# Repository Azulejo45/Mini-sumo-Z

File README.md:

### ┍━━━━━━━━━━━━»•»  «•«━━━━┑
#   ┕Zangetsu-MiniSumo┙        

### - Proyecto de mini sumo con la capacidad de ser controlado de manera bluetooth y automata. Equipado con 4 sensores:  2 laterales, 1 frontal y uno en la parte inferior, el de piso.
♥

## ..••°°━✦❘༻⋞ 〈 Autores  〉 ⋟༺❘✦━━°°••..

- ⋆ˊˎ-   ┌──༺♥༻❀**Velazquez Joaquim**❀༺♥༻
  
- ⋆ˊˎ-  **Rodriguez Thiago**

### *---16/3/2026---*

♥
## •*¨*•.¸¸☆*･ﾟ Especificaciones generales ﾟ･*☆¸¸.•*¨*•

˚₊· ͟͟͞͞➳❥ Dimensiones del robot: 10 cm x 10 cm x 4,5 cm.

˚₊· ͟͟͞͞➳❥ Consumo total: 7,4V.

˚₊· ͟͟͞͞➳❥ Corriente total: 800mA.

˚₊· ͟͟͞͞➳❥ Material de la carrocería: PLA.

˚₊· ͟͟͞͞➳❥ Peso (aproximado): 300g.
## ✭∞∞∞∞∞∞∞∞✭∞∞•,¸,.·' ✩ '·.,¸,•∞∞✭∞∞∞∞∞∞∞∞✭

♥
## Objetivo del proyecto
### ✩°｡𓂃𓏧︶︶︶︶︶︶︶︶┈୨•♡•୧┈︶︶︶︶︶︶︶𓂃𓏧｡°✩
_El objetivo principal de este proyecto es poner a prueba lo aprendido en años anteriores y este, pudiendo aplicarlo en el proceso de preparacion y  creacion de un robot modelo Mini-Sumo, siguiendo el reglamento de la liga nacional de robotica LNR, para que se encuentre en condiciones en poder participar en una competencia de esta misma_
### ✩°｡𓂃𓏧⌒⌒⌒⌒⌒⌒⌒⌒┈୨•♡•୧┈⌒⌒⌒⌒⌒⌒⌒⌒𓂃𓏧｡°✩
\
\
.
### ∘₊✧───∘₊✧───•-•⟮ ◆ ⟯•-•───✧₊∘───✧₊∘
## ˗ˏˋ ꒰ **Este proyecto fue realizado con algunos componentes en donde se puede llegan a encontrar:** ꒱ ˎˊ˗

- Micro: Esp32 C3 super mini.
 > Memoria: 400 KB SRAM, 4 MB Flash.Conectividad: Wi-Fi (2,4 GHz).\
 > Bluetooth 5.0 LE (Low Energy).\
 > Alimentación: Funciona a 3,3 V con entrada USB-C de 5 V.

- Bateria de Lipo.
 > Almacenamiento: 7,4V.\
 > 2 celdas (3,7V por celda)
  
- Sensor de piso: TCRT5000.
 > Voltaje de operación: 3.3V-5V.\
 > Dimensiones: 31 mm × 13 mm × 2 mm.\
 > Rango de detección: 30° más amplio.

- Sensor detector de obstáculos: HC-sr04.
 > Voltaje de operacion: 5V.\
 > Cantidad de pines: 4.\
 > Distancia de deteccion: 2 a 450cm.
 
- Motores: Micro motores Pololu 250RPM.
 > Dimensiones: 26x10x12mm.\
 > Voltaje de operacion: 6V.\
 > Torque maximo: 333Nm (Newton - metro).

- Puente H: DRV8833.
 > Dimensiones: 4 mm × 18,1 mm × 21,1 mm.\
 > Voltaje de operacion: 2.7V-10.8V.\
 > Corriente máxima de salida: 1,5A.
 ### ∘₊✧───∘₊✧──────✧₊∘───✧₊∘
\
.
## ╔══✬✩══╡˚✧Componentes utilizados✧˚╞══✩✬══╗
- ➸ *Esp32 C3 super mini.*
- ➸ *Bateria de Lipo.*
- ➸ *TCRT5000.*
- ➸ *HC-sr04.*
- ➸ *Micro motores Pololu 250RPM.*
- ➸ *DRV8833.*
## ╚═══*+:｡ . ｡:+*═══✮❁•°❀°•❁✮═══*+:｡ . ｡:+*═══╝
\
\
\
\
\
♥
# Diseño del circuito

## Descripcion del funcionamiento

El minisumo utiliza tres sensores para guiarse, con dos ubicados en los costados; otro en la parte frontal. Cuando un objeto entra en el rango del sensor frontal, el minisumo avanza hasta chocar contra dicho objeto. Esto siempre se cumple hasta que se quite la orden.\
Cuando uno de los sensores en los costados detectan algo cerca, se posiciona para estar de frente al objeto, retrocediendo y girando en direccion paralela a este.
Este mismo, utiliza el sensor de piso para evitar salirse del dohyo, detectyando la franja limite y volviendo para no estar tan vulnerable a cualquier empuje que lo saque de juego.

## Esquematico

## Layout de PCB

# Pasos a seguir para armar el mini-sumo
## ˚*•̩̩͙✩•̩̩͙*˚＊˚*•̩̩͙✩•̩̩͙*˚＊˚*•̩̩͙✩•̩̩͙*˚＊˚*•̩̩͙✩•̩̩͙*˚＊˚*•̩̩͙✩•̩̩͙*˚

### Primero elistaremos las herramientas necesarias para llevar a cabo la placa.

.°-> Un recipiente\
.°-> Percloruro\
.°-> Una agujereadora\
.°-> Una placa de cobre\
.°-> Papel fotografico\
.°-> Tinta Tonel\
.°-> Una impresora(Para imprimir el diseño PCB)\
.°-> Cable USB-C (Para cargar el codigo.)

 ### -|preparación de la placa:

1) Descargar el archivo de PCB de "Zungetosu(MiniSumo).kicad_pcb".\
2). Imprimir el PCB en una hoja fotográfica (como lo son las hojas de revista) con tinta "tonel".\
3) Proceda a planchar el PCB a la placa del lado del cobre.\
4) Revisar que el diagrama del PCB se haya pegado correctamente retirando la hoja fotográfica y cualquier excendete de esta (Utilice agua para remover con facilidad el papel).\
5) Sumergir la placa en un recipiente con percloruro.\
6) Dejarlo descansar un tiempo (Resivar periodicamente el cobre de la placa)\
7) Cuando el cobre se haya disuelto y solo quede el diseño, retirarlo con CUIDADO (Es un liquido corrosivo; dificil de quitar de la ropa).\
8) Limiparlo la placa con agua para quitar el excedente de percloruro.

 ### -|Soldar los componentes en la placa ya hecha en el siguiente orden:
 
1. Capacitores SMD
2. Pineras
3. Borneras
4. Resistencias SMD
5. Regulador AMS1117 5V

 ### Medidas de seguridad.

.°-> El percloruro es un tanto corrosivo, capáz de manchar con facilidad la ropa y otra prendas.\
.°-> Cuando vaya a hacer agujeros en la placa, tiene que ser en una superficie solida. Es probable que la placa pueda salir dispara en una base dispareja o inquieta.\
.°-> Mientra planche, este atento a no quemar completamente el papel. Podria causar un incendio.

### Tipo de soldadura/ensamble

Todos los componentes deben fijados a la placa mendiante "soldadura de ola", el cual se utiliza para componentes de orificio pasante (THT). Los componentes debe ser introducidos desde el lado de la placa lisa y sin diseño,para ser soldados en el cobre que se encuentra del otro lado.
En las pineras que estan direccionadas en horizontal, se debe colocar el ESP32(integrado).
En la pineras que se encuentran en vertical, el DRV8833.

### -|Carroceria

1. Descargar el modelo 3D de la carroceria ubicada en HARDARE.
2. Descargar un modelo 3D de dos braquets y 2 ruedas con un radio de 20mm.
3. Imprimir ambos archivos.
4. Comprar cuatro tornillos para tuerca M3, 6 tuercas M3 y 2 prisioneros M3.
5. Unir la carroseria con los braquets mediante 4 tornillos M3 y 4 tuercas M3.

### -|Codigo

El codigo establece las instrucciones que ejecutara el integrado para poder accionar y manejar al mini-sumo.\
este es bastante simple y considera los 4 sensores teniendo en cuenta que:

.°-> No debe salir del tatami.
.°-> Debe atacar y empujar al otro mini-sumo fuera del area.
.°-> Esquivar al mini-sumo rival cuando se le de la orden.

#### -|Compilacion/Carga

Cuando la placa ya este monatada, se utilizara un cable USB tipo C para conectar el integrado(ESP32) a un ordenador. Mediante el programa [Arduino IDE](https://www.arduino.cc/en/software). Copie el codigo que se encuentra en este repositorio y pueguelo en el programa. En el apartado superior encontrara 4 botones.\
El primero es para verificar si el programa tiene errores\
El segundo es para subir el codigo al integrado\
El tercero no es importante para esto.\
El cuarto es para poder seleccionar la placa y el puerto\
En este ultimo, busque el siguiente modelo: ESP32_C3_SUPER_MINI, y seleccionelo. En caso de no encontrarlo, use el "ESP32 C3 DEV MODULE". Junto a eso, seleccione el puerto USB por el cual esta conectado a su ordenador(Se cuenta de izquierda a derecha).\
Ahora, verifique el codigo por el primero boton de la parte superior. Si marca algun error, copie el codigo entero de nuevo y vuelva a pegarlo./
Una vez verificada la funcionalidad del codigo, utilice el segundo boton presente para poder subir el codigo al integrado de la placa. Si hay alguno otro error durante este proceso, consulte internet.

#### -[Librerias
- Para poner librerias, dirigase al lateral izquierdo de la interfaz de Arduino IDE, y seleccione el tercer boton (que contiene un simbolo con libros).

#### -[Datasheets/Referencias

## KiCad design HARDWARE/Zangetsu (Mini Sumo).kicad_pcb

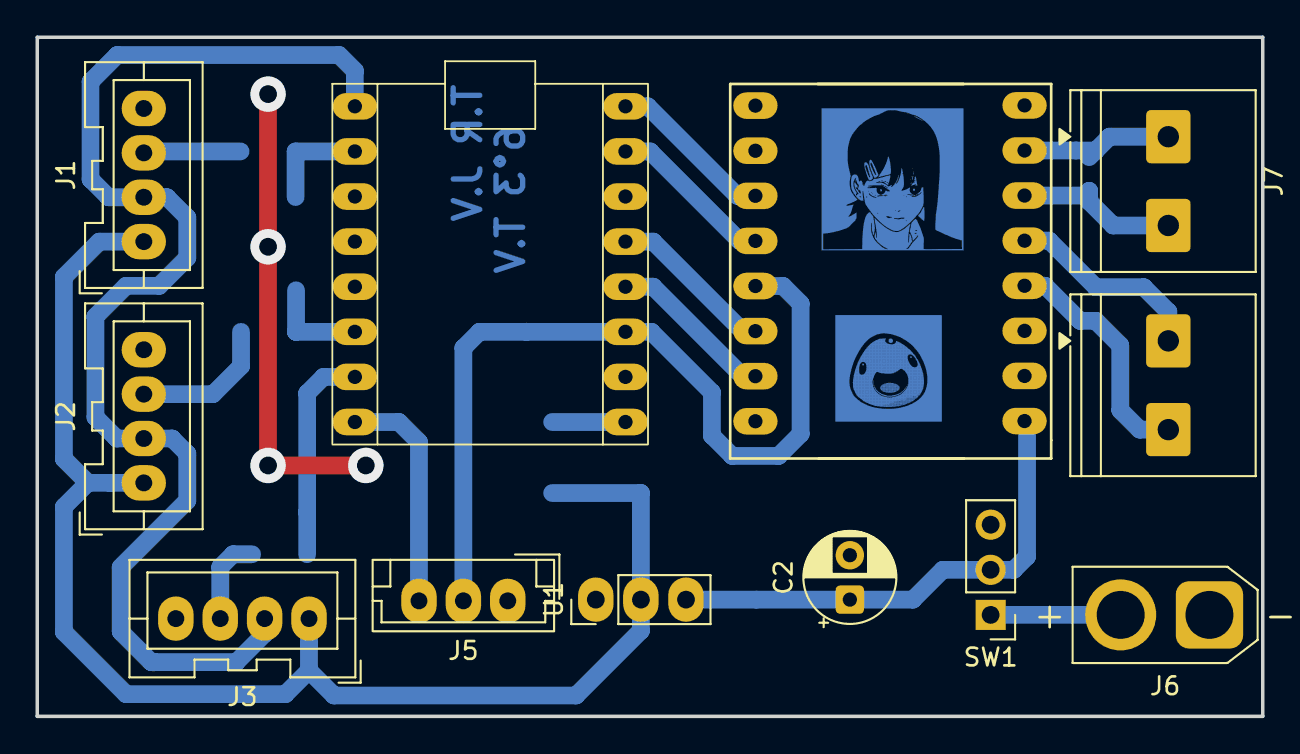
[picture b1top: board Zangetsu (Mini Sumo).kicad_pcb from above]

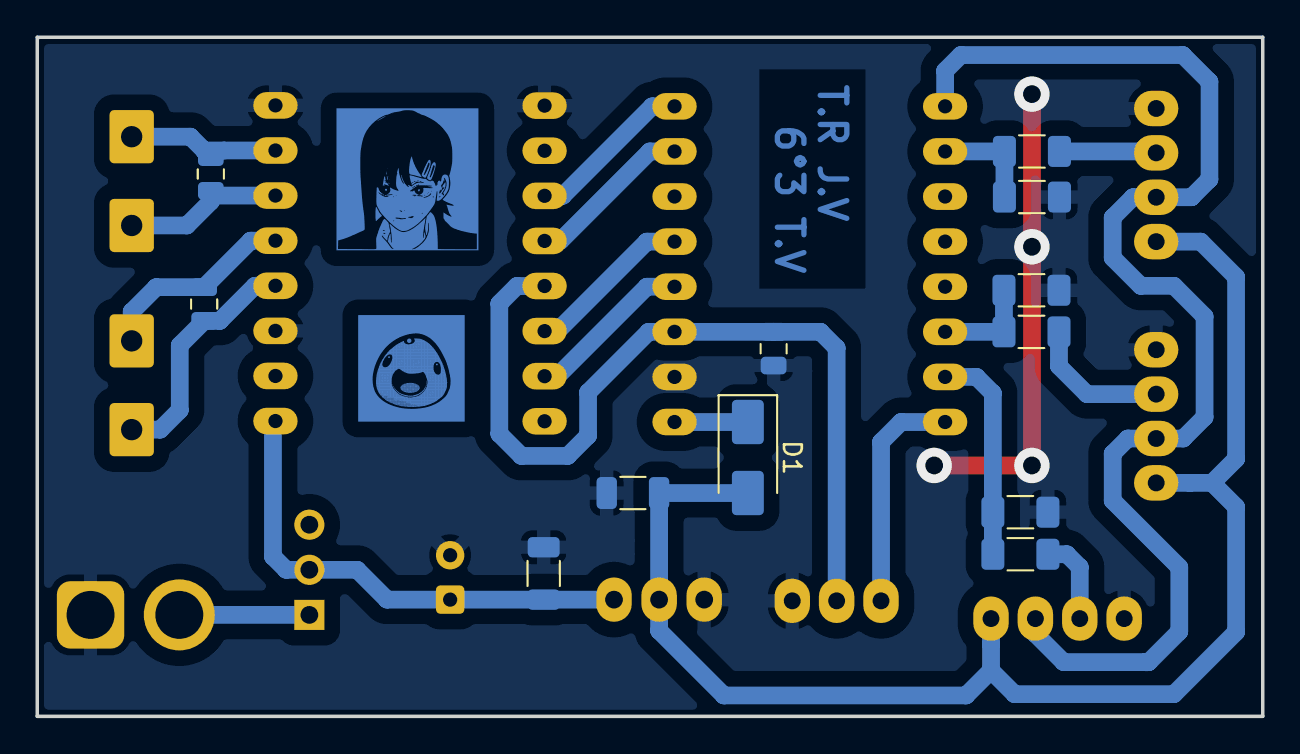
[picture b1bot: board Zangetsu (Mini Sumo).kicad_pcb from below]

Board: 2 copper layers, 69.0 x 38.2 mm, 24 parts (12 on the bottom side), 22 nets.

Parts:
C1, C4, C6: 100nF; C_0805_2012Metric
C2: 100uF; CP_Radial_D5.0mm_P2.50mm
C3, C5: 10uF; C_1206_3216Metric
D1: 1N4007; D_SMA
DRV1: DRV8833_Pololu
ESP32_C3_SM1: ESP32_C3_SM
J1, J2, J3: JST_XA_B04B-XASK-1_1x04_P2.50mm_Vertical
J4, J7: TerminalBlock_Philmore_TB132_1x02_P5.00mm_Horizontal
J5: JST_EH_B3B-EH-A_1x03_P2.50mm_Vertical
J6: AMASS_XT30U-F_1x02_P5.0mm_Vertical
R1, R4, R6: 2k; R_1206_3216Metric_Pad1.30x1.75mm_HandSolder
R2, R3, R5: 1k; R_1206_3216Metric_Pad1.30x1.75mm_HandSolder
SW1: SW_DPST_x2; PinHeader_1x03_P2.54mm_Vertical
U1: AMS1117; PinHeader_1x03_P2.54mm_Vertical

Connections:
+3.3V: C1.2, DRV1.13 (STBY), ESP32_C3_SM1.11 (3V3), J5.2
+5V: C5.1, D1.2 (A), J1.1, J2.1, J3.1, U1.2 (VO)
/ECHO1: ESP32_C3_SM1.2 (GPIO6), R1.2, R2.2
/ECHO2: ESP32_C3_SM1.6 (GPIO10), R3.2, R4.2
/ECHO3: ESP32_C3_SM1.7 (GPIO20), R5.2, R6.2
/IN1: DRV1.15 (AIN2), ESP32_C3_SM1.12 (GPIO4)
/IN2: DRV1.14 (AIN1), ESP32_C3_SM1.13 (GPIO3)
/IN3: DRV1.12 (BIN1), ESP32_C3_SM1.15 (GPIO1)
/IN4: DRV1.11 (BIN2), ESP32_C3_SM1.16 (GPIO0)
/M1: C4.2, DRV1.4 (AO1), J4.2
/M2: C4.1, DRV1.5 (AO2), J4.1
/M3: C6.1, DRV1.7 (BO1), J7.1
/M4: C6.2, DRV1.6 (BO2), J7.2
/OUT: ESP32_C3_SM1.8 (GPIO21), J5.3
/TRIGGER: ESP32_C3_SM1.1 (GPIO5), J1.2, J2.2, J3.2
GND: C1.1, C2.2, C3.1, C5.2, DRV1.3 (GND), DRV1.8 (GND), DRV1.9 (GND), ESP32_C3_SM1.10 (GND), J1.4, J2.4, J3.4, J5.1, J6.1, R1.1, R4.1, R6.1, U1.1 (ADJ)
unnamed: D1.1 (K), ESP32_C3_SM1.9 (5V)
unnamed: J1.3, R2.1
unnamed: J2.3, R3.1
unnamed: J3.3, R5.1
unnamed: J6.2, SW1.1 (A)
VCC: C2.1, C3.2, DRV1.1 (VM), SW1.2 (B), U1.3 (VI)

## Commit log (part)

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2026-04-07 Rename README to README.md
